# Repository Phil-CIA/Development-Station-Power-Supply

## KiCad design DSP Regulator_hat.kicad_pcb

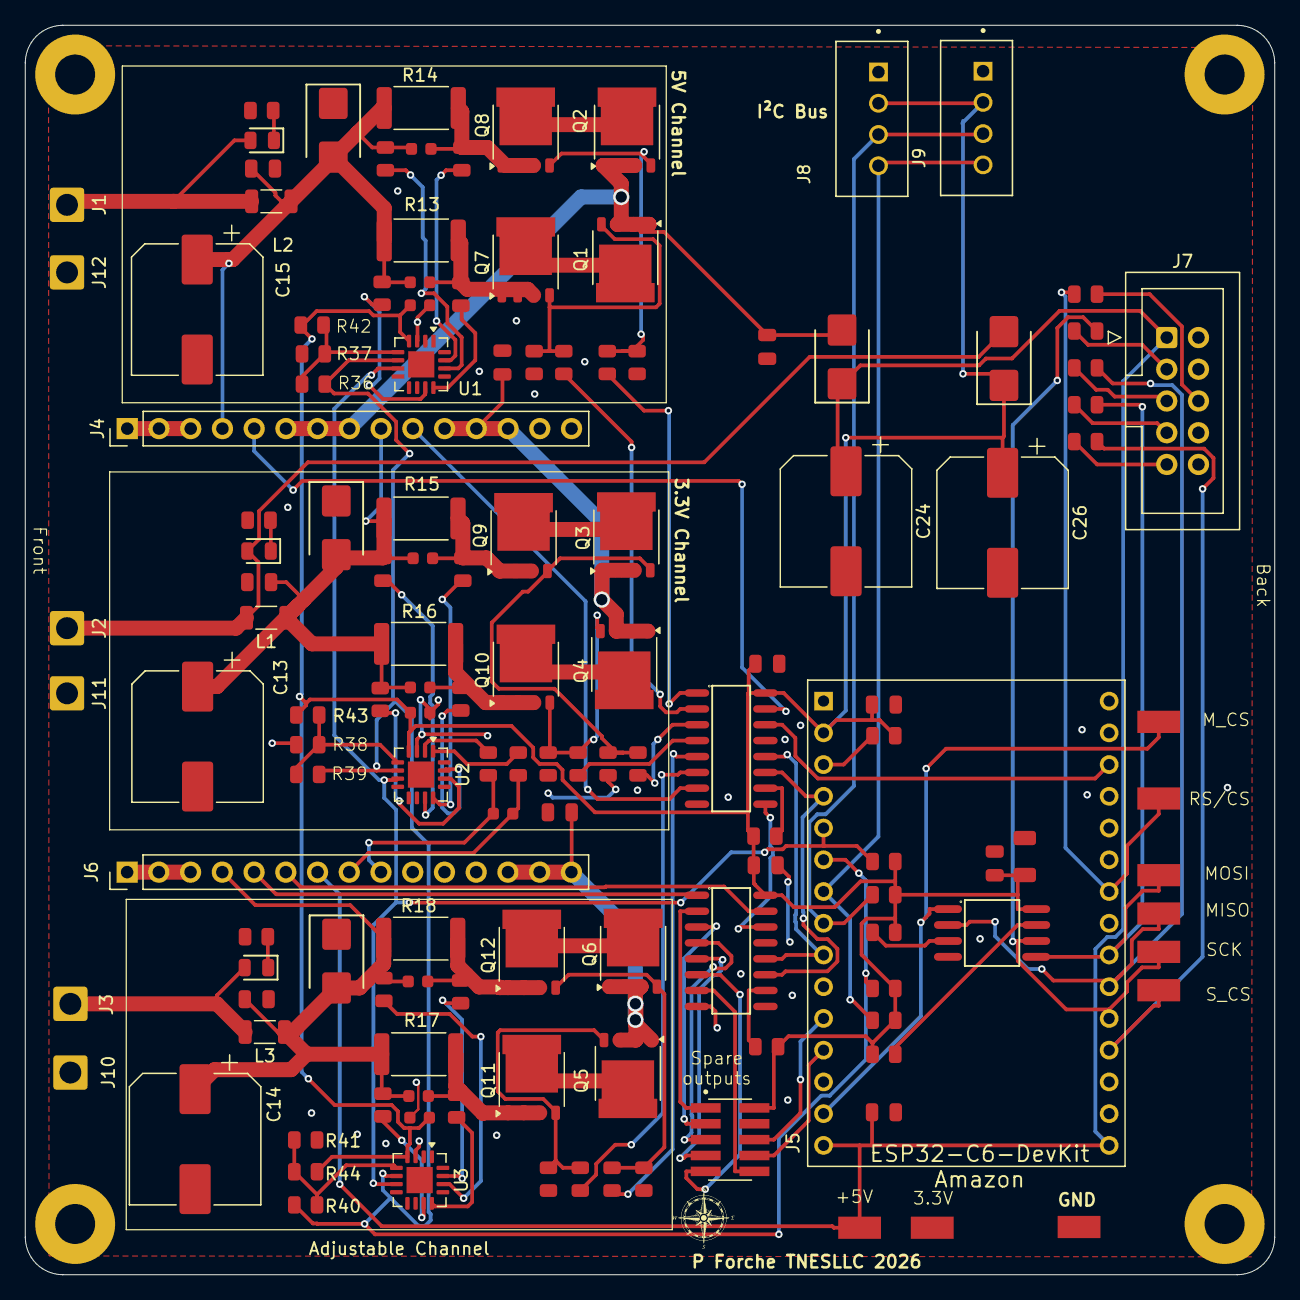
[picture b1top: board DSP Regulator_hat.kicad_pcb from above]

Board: 2 copper layers, 100.0 x 100.0 mm, 141 parts (0 on the bottom side), 94 nets.

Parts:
5mm1: 5mm LOGO
C1, C2, C3, C8, C11, C12: 10uF; C_0805
C4, C5, C6, C7, C9, C10, C16, C17, C18, C19: 100nf; C_0603
C13, C14, C15, C24, C26: 470uf 25v; CP_Elec_10x10
C20: 100uF; C_1206
C21, C22, C23, C25, C27: 100nF; C_0805
CS1: 5015; KEYSTONE_5015
D1, D7: SS54B; D_SMB
D2, D3, D4: SMBJ6.0A; D_SMB
D5, D6, D8: Green; D_0805
H1, H2, H3, H4: MountingHole_Pad; MountingHole_3.2mm_M3_Pad
J1, J2: Wire con; SolderWire-1sqmm_1x01_D1.4mm_OD2.7mm
J3, J10, J11, J12: W; SolderWire-1sqmm_1x01_D1.4mm_OD2.7mm
J4: Left Side; PinHeader_1x15_P2.54mm_Vertical
J5: Conn_01x06_Socket; AMPHENOL_SPI HDR
J6: Right Side; PinHeader_1x15_P2.54mm_Vertical
J7: Front Panel; IDC-Header_2x05_P2.54mm_Vertical
J8, J9: I2C bus; JST_B4B-XH-A
L1: Ferrite3.5A 20mΩ; L_1206_3216Metric
L2, L3: L_Ferrite 3.5A 20mΩ; L_1206_3216Metric
MISO1: 5015; KEYSTONE_5015
MOSI1: 5015; KEYSTONE_5015
Memory_CS1: 5015; KEYSTONE_5015
Q1, Q2, Q3, Q6, Q7, Q8, Q9, Q12: PSMN5R2-60YL; LFPAK56
Q4, Q10, Q11: PSMN5R2; LFPAK56
Q5: PSMN5R2'; LFPAK56
R1, R2, R3, R4, R5, R6: 100kΩ; R_0805
R7, R8, R9, R10, R11, R12: 100Ω; R_0805
R13, R15, R17: 20mΩ 2W; R_2512_6332Metric
R14, R16, R18: 200mΩ 2W; R_2512_6332Metric
R19, R20, R21, R22, R23, R24, R25, R26, R27, R28, R29, R30, R34, R35: 10Ω; R_0805
R31, R32, R33: 270Ω; R_0805
R36, R37, R38, R39, R40, R41, R42, R43, R44: 0Ω; R_0805
R45, R46, R47, R49, R50: 10kΩ; R_0805
R48, R51, R52, R53, R54: 33Ω; R_0805
R55, R56, R57, R58: 4.7kΩ; R_0805
SCK1: 5015; KEYSTONE_5015
TP1, TP2_+5V1: 5015; KEYSTONE_5015
TP_+3.3V1: 5015; KEYSTONE_5015
T_IRQ1: 5015; KEYSTONE_5015
U1, U2, U3: INA3221-AIRGVR; Texas_RGV0016A_VQFN-16-1EP_4x4mm_P0.65mm_EP2.1x2.1mm
U4, U5: 74HC595D; SOIC-16_L9.9-W3.9-P1.27-LS6.0-BL
U6: W25Q128; SOIC-8_L5.3-W5.3-P1.27-LS8.0-BL
U7: ESP32-C6-DevKitM-1; ESP32-C3-DevKitM-1

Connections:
3.3_Select: J6.6, U5.15 (Q0)
3V3_ESP: C17.1, C18.1, C19.1, C20.1, C21.2, C22.2, C23.1, C26.1, C27.1, D7.1, J5.2, J8.2, J9.2, R42.2, R43.2, R44.2, R45.2, R46.2, R47.2, R49.1, R50.2, R55.2, R56.2, R57.2, R58.2, U1.4 (VS), U2.4 (VS), U3.4 (VS), U4.16 (VCC), U5.16 (VCC), U6.8 (VCC), U7.2 (3V3)
ISET_MPU_3V3: J4.10, U4.7 (Q7)
ISET_MPU_Channel_3: J6.5, U5.1 (Q1)
Memory_CS: Memory_CS1.TP, U6.1 (CS#), U7.14 (GPIO13)
+3.3V_Reg: C2.1, J4.11, J4.12, J4.13, Q3.1 (S), Q3.2 (S), Q3.3 (S), Q4.1 (S), Q4.2 (S), Q4.3 (S)
+3v3V_Hi_Range: R27.2, U2.12 (IN+1)
+3v3V_low_Range: R30.2, U2.15 (IN+2)
+5V_Control: C24.1, C25.1, D1.1, J6.7, J7.1, TP2_+5V1.TP, U7.15 (5V), U7.16 (5V)
+5V_Hi_Range: R19.2, U1.12 (IN+1)
+5V_low_Range: R22.2, U1.15 (IN+2)
+5V_reg: C1.1, D1.2, J4.6, J4.7, J4.8, Q1.1 (S), Q1.2 (S), Q1.3 (S), Q2.1 (S), Q2.2 (S), Q2.3 (S)
+V Adj Channel: C3.1, J6.13, J6.14, J6.15, Q5.1 (S), Q5.2 (S), Q5.3 (S), Q6.1 (S), Q6.2 (S), Q6.3 (S)
+V_Hi_Range: R23.2, U3.12 (IN+1)
+V_low_Range: R26.2, U3.15 (IN+2)
-3v3V_Hi_Range: R28.2, U2.11 (IN-1)
-3v3V_low_Range: R29.2, U2.14 (IN-2)
-5V_Hi_Range: R20.2, U1.11 (IN-1)
-5V_low_Range: R21.2, U1.14 (IN-2)
-V_Hi_Range: R24.2, U3.11 (IN-1)
-V_low_Range: R25.2, U3.14 (IN-2)
Channel _3_High_range: R11.2, U4.6 (Q6)
Channel _3_low_range: R12.2, U4.5 (Q5)
ESP- GPIO 3.3V High: R9.2, U4.3 (Q3)
ESP- GPIO 3.3V Low: R10.2, U4.4 (Q4)
ESP- GPIO 5V Hi: R8.2, U4.1 (Q1)
ESP- GPIO 5V Low: R7.2, U4.2 (Q2)
Feedback 3.3: C8.1, C9.2, C10.1, C13.1, D2.2, J4.9, L1.1, R15.2, R16.2, R28.1, R29.1
Feedback 5V: C4.1, C5.2, C12.1, C15.1, D4.2, J4.4, L2.1, R13.2, R14.2, R20.1, R21.1
Feedback Adj Channel: C6.2, C7.1, C11.1, C14.1, D3.2, J6.4, L3.1, R17.2, R18.2, R24.1, R25.1
GND: C1.2, C2.2, C3.2, C8.2, C11.2, C12.2, C13.2, C14.2, C15.2, C17.2, C18.2, C19.2, C20.2, C21.1, C22.1, C23.2, C24.2, C25.2, C26.2, C27.2, D2.1, D3.1, D4.1, H1.1, H2.1, H3.1, H4.1, J4.1, J4.2, J4.3, J5.4, J6.1, J6.2, J6.3, J7.2, J7.4, J7.8, J7.10, J8.1, J9.1, J10.1, J11.1, J12.1, R1.2, R2.2, R3.2, R4.2, R5.2, R6.2, R31.2, R32.2, R33.2, R37.2, R38.2, R41.2, TP1.TP, U1.3 (GND), U2.3 (GND), U3.3 (GND), U4.8 (GND), U4.13 (OE#), U5.8 (GND), U5.13 (OE#), U6.4 (GND), U7.1 (GND), U7.17 (GND), U7.30 (GND)
GPIO10: J5.6, U7.11 (GPIO10)
GPIO11: J5.8, U7.12 (GPIO11)
ISET_MPU_5V: J4.5, U4.15 (Q0)
Incoming (+): C16.1, J6.9, R34.1
Incoming (-): C16.2, J6.8, R35.1
I²C SCL_0: R36.1, R39.1, R40.1, R55.1, U1.6 (SCL), U2.6 (SCL), U3.6 (SCL), U7.6 (GPIO6)
I²C SCL_1: J8.4, J9.4, R57.1, U7.7 (GPIO7)
I²C SDA_0: R56.1, U1.7 (SDA), U2.7 (SDA), U3.7 (SDA), U7.5 (GPIO5)
I²C SDA_1: J8.3, J9.3, R58.1, U7.8 (GPIO0)
unnamed: C4.2, Q8.1 (S), Q8.2 (S), Q8.3 (S), R14.1, R22.1
unnamed: C5.1, Q7.1 (S), Q7.2 (S), Q7.3 (S), R13.1, R19.1
unnamed: C6.1, Q11.1 (S), Q11.2 (S), Q11.3 (S), R17.1, R23.1
unnamed: C7.2, Q12.1 (S), Q12.2 (S), Q12.3 (S), R18.1, R26.1
unnamed: C9.1, Q9.1 (S), Q9.2 (S), Q9.3 (S), R15.1, R27.1
unnamed: C10.2, Q10.1 (S), Q10.2 (S), Q10.3 (S), R16.1, R30.1
unnamed: D5.1, R31.1
unnamed: D6.1, R32.1
unnamed: D8.1, R33.1
unnamed: J7.3, R51.1
unnamed: J7.5, R52.1
unnamed: J7.6, R48.2
unnamed: J7.7, R53.1
unnamed: J7.9, R54.1
unnamed: Q1.5 (D), Q7.5 (D)
unnamed: Q1.4 (G), Q7.4 (G), R1.1, R7.1
unnamed: Q2.5 (D), Q8.5 (D)
unnamed: Q2.4 (G), Q8.4 (G), R2.1, R8.1
unnamed: Q3.5 (D), Q9.5 (D)
unnamed: Q3.4 (G), Q9.4 (G), R3.1, R9.1
unnamed: Q4.5 (D), Q10.5 (D)
unnamed: Q4.4 (G), Q10.4 (G), R4.1, R10.1
unnamed: Q5.5 (D), Q11.5 (D)
unnamed: Q5.4 (G), Q11.4 (G), R5.1, R11.1
unnamed: Q6.5 (D), Q12.5 (D)
unnamed: Q6.4 (G), Q12.4 (G), R6.1, R12.1
unnamed: R36.2, R37.1, R42.1, U1.5 (A0)
unnamed: R38.1, R39.2, R43.1, U2.5 (A0)
unnamed: R34.2, U2.2 (IN+3)
unnamed: R35.2, U2.1 (IN-3)
unnamed: R40.2, R41.1, R44.1, U3.5 (A0)
unnamed: R45.1, U4.10 (MR#)
unnamed: U4.9 (Q7S), U5.14 (DS)
unnamed: R46.1, U5.10 (MR#)
unnamed: J5.1, U5.2 (Q2)
unnamed: J5.3, U5.3 (Q3)
unnamed: J5.5, U5.4 (Q4)
unnamed: J5.7, U5.5 (Q5)
unnamed: J5.9, U5.6 (Q6)
unnamed: J5.10, U5.7 (Q7)
unnamed: R50.1, U6.3 (IO2)
unnamed: R47.1, U6.7 (IO3)
unnamed: R49.2, U7.3 (EN/RESET)
RTS/CTS: R48.1, T_IRQ1.TP, U7.24 (GPIO23)
SPI SCK: R51.2, SCK1.TP, U6.6 (CLK), U7.20 (GPIO19)
SPI_CS: CS1.TP, R54.2, U7.19 (GPIO18)
SPI_MISO: MISO1.TP, R52.2, U6.2 (DO), U7.21 (GPIO20)
SPI_MOSI: MOSI1.TP, R53.2, U6.5 (DI), U7.22 (GPIO21)
SR_CLK: U4.11 (SHCP), U5.11 (SHCP), U7.4 (GPIO4)
SR_Data: U4.14 (DS), U7.28 (GPIO3)
SR_Latch: U4.12 (STCP), U5.12 (STCP), U7.9 (GPIO1)
V_out +3V3: D5.2, D7.2, J2.1, L1.2
V_out +5V: D6.2, J1.1, L2.2
V_out +CH3: D8.2, J3.1, L3.2
